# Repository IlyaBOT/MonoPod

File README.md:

# MonoPod

**MonoPod** — самодельный портативный музыкальный плеер в духе классических iPod. Это одновременно учебный проект и личная разработка: электроника, корпус, прошивка и программа для синхронизации музыки с компьютером.

Плеер построен на **ESP32-S3 N16R8**. У него цветной дисплей ST7735S (160 × 128), сенсорное колесо, физические кнопки, microSD, аудиовыход через PCM5102A и синхронизация по USB или Wi-Fi.

## Что лежит в репозитории

| Раздел | Содержимое |
| --- | --- |
| [firmware/](firmware/) | Прошивка для ESP32 / ESP32-S3, инструменты и тесты. Текущая версия: **0.10.7.5**. |
| [desktop/](desktop/) | **MonoPod Desktop 1.3.0** — Windows-приложение для передачи файлов, работы с медиатекой, темами и обновления прошивки. |
| [hardware/](hardware/) | Корпус, 3D-модели, детали для печати и имеющиеся файлы KiCad. |

## Быстрый старт

**Прошивка:** откройте [`firmware/DIY_iPod_Mono/DIY_iPod_Mono.ino`](firmware/DIY_iPod_Mono/DIY_iPod_Mono.ino) в Arduino IDE. Список библиотек, настройки платы и важные ограничения приведены в [инструкции прошивки](firmware/README.md).

**Программа для ПК:** откройте [`desktop/MonoPod.Desktop.sln`](desktop/MonoPod.Desktop.sln) в Visual Studio 2022 или соберите через .NET SDK 8. Подробности — в [desktop/README.md](desktop/README.md).

**Корпус и платы:** начните с [hardware/README.md](hardware/README.md).

## Состояние проекта

Разработка продолжается. Поддержка некоторых возможностей зависит от модели ESP32 и выбранной конфигурации. Например, **Bluetooth Classic/A2DP не поддерживается самим ESP32-S3**; соответствующий режим предназначен для оригинального ESP32.

Прошивка и электроника — прототип: перед повседневным использованием необходима проверка питания, зарядки, подключения аккумулятора и поведения при разряде. Архивы старых версий удалены из текущего дерева, но доступны в истории Git.

## Авторство и лицензии

MonoPod — независимый DIY-проект, вдохновлённый устройствами iPod; он не является продуктом Apple. Лицензионные файлы, включённые в исходники и ресурсы, находятся рядом с ними: [COPYING](firmware/DIY_iPod_Mono/COPYING), [шрифты](firmware/DIY_iPod_Mono/LICENSE-MONOFONT.txt), [компоненты Desktop](desktop/docs/THIRD_PARTY_NOTICES.md). Условия для всех частей репозитория в целом отдельно не заявляются.

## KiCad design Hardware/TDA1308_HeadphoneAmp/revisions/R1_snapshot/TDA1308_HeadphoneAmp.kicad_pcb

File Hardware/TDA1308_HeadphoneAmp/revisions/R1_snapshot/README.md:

# MonoPod: усилитель наушников TDA1308, R1

Создано 27.10.2026 в KiCad 10.0.6. Основной проект: `TDA1308_HeadphoneAmp.kicad_pro`; редактируемые схема и PCB находятся рядом. Папки `libraries/`, таблицы `sym-lib-table` и `fp-lib-table` содержат реальные символы, footprints и модели из установленного KiCad, поэтому проект можно переносить целиком.

## Что выполнено и что подтверждено

- Двухслойная PCB 45 x 25 мм, FR4 1,6 мм. Компоненты сверху; большие электролиты вдоль верхнего края.
- Основа: [NXP TDA1308 Rev.5, Fig.4, стр.6](https://www.nxp.com/docs/en/data-sheet/TDA1308.pdf). Инвертирующие каскады, VREF, питание и полярности сверены по рисунку; различия перечислены в `validation/datasheet_comparison.md`.
- Свежие ERC и DRC: 0 нарушений, 0 незавершённых соединений, 0 расхождений PCB со схемой. Отчёты в `validation/`. Исключения DRC не добавлялись.
- Проверены все площадки и выводы по экспортированному нетлисту, полярности C1/C2/C6/C7, pin 1 U1 и конфигурации ATT/DIRECT. `engineering_audit.json` и `calculations.json` содержат измеренные CAD-параметры и расчёты.
- Это законченные CAD-файлы и производственные экспорты. Физический образец не изготовлен и не испытан. ERC/DRC не подтверждают исправность выпаянной микросхемы, устойчивость с конкретным кабелем, THD, шум или механическое размещение в корпусе MonoPod.

## Питание и провода

Штатно подать стабилизированные 3,3 В. Подача 5 В допустима только после успешных испытаний на стенде; 5 В идут только на эту плату, а не на GPIO ESP32. Не превышать 5 В в этом проекте. Общая земля для питания, PCM5102A и наушников. Разъём 3,5 мм устанавливается отдельно.

| Площадка | Надпись | Назначение |
|---|---|---|
| J1 | VCC | VDD, питание 3,3 В |
| J2 | GND | Земля питания и PCM5102A |
| J3 | LIN | Левый линейный сигнал PCM5102A |
| J4 | RIN | Правый линейный сигнал PCM5102A |
| J5 | GND | Общий контакт наушников |
| J6 | LOUT | Левый контакт наушников, после C6 |
| J7 | ROUT | Правый контакт наушников, после C7 |

Смотреть на лицевую сторону: входные провода слева, выходные справа. Отверстия проводов фактически 1,15 мм, площадки 2,3 мм; AWG26-30 подходят. `D0.9mm` в имени footprint обозначает размер провода, а не диаметр сверла. Закрепить провода от натяжения в корпусе. Монтажных отверстий нет. Провода сигнал/земля вести рядом, вдали от ESP32, антенны и импульсных цепей питания.

## Режим входа: переключать только при снятом питании

| Канал / режим | Установить 0 Ом | Не устанавливать / снять |
|---|---|---|
| L ATTENUATED, по умолчанию | R15, R16 | R19 |
| R ATTENUATED, по умолчанию | R17, R18 | R20 |
| L DIRECT | R19 | R15 И R16 |
| R DIRECT | R20 | R17 И R18 |

R3/R4 и R5/R6 остаются на местах. Две снимаемые перемычки полностью отключают соответствующий делитель и от источника, и от выбранного входа. В DIRECT резистор 3,3 кОм не шунтирует источник. Одновременная установка ATT и DIRECT недопустима; электрической механической защиты от ошибочной пайки нет. Каналы можно конфигурировать отдельно. Вход DIRECT при полной амплитуде PCM5102A вызовет клиппинг: начинать с программно уменьшенной громкости.

Изолированный делитель 10 кОм / 3,3 кОм даёт -12,1 дБ, но вход 3,9 кОм нагружает его. Полная схема в ATT имеет около -16,4 дБ до выходного резистора и -17,0 дБ до наушников 32 Ом на средних частотах. При 2,1 В RMS на входе расчётно получается около 0,298 В RMS / 2,8 мВт на канал. Это расчёт линейной схемы, не измерение громкости и не гарантия максимальной мощности. Оба канала инвертированы одинаково; взаимная полярность стерео сохраняется.

R7/R9 и R8/R10 = 3,9 кОм: номинальное отношение резисторов активной ступени -1. В режиме ATT сопротивление источника дополнительно влияет на суммарное усиление. C4/C5 неполярные, 4,7 мкФ / 25 В X7R 1206; выбрать изделие с фактической ёмкостью не менее 2,2 мкФ при постоянном смещении до 2,5 В. Номинальный входной срез: около 5,3 Гц в ATT и 8,7 Гц в DIRECT при 4,7 мкФ, выше при снижении эффективной ёмкости.

## Конденсаторы и имеющиеся детали

| Ref | Номинал по умолчанию | Место / максимальный диаметр | Полярность |
|---|---|---|---|
| C1 | 22 мкФ, >=10 В | Радиальный D5, шаг 2,0 мм | + к VREF, - к GND |
| C2 | 100 мкФ, >=10 В | Радиальный D6,3, шаг 2,5 мм | + к VDD, - к GND |
| C3 | 100 нФ, 25 В, X7R | 0805 | Неполярный |
| C4/C5 | 4,7 мкФ, 25 В, X7R | 1206 | Неполярные |
| C6/C7 | 220 мкФ, >=10 В | Радиальный D8, шаг 3,5 мм | + к усилителю через R11/R12, - к наушникам |

C6/C7 можно заменить на 470 мкФ / >=10 В в том же габарите. Ваши выпаянные 100 мкФ / 25 В электрически подходят для C2 и как временная замена C6/C7; корпус должен физически помещаться. Для C2 требуется D<=6,3 мм, для C6/C7 D<=8 мм. Шаг 2,5 мм у меньшего конденсатора можно аккуратно развести до 3,5 мм для C6/C7, не нагружая выводы у резиновой пробки. Не изгибать выводы вплотную к корпусу. Монтаж стоя; укладка крупных конденсаторов лёжа внутрь платы не предусмотрена. Высоту и место в корпусе измерить до сборки. 3D-модели библиотечные и не доказывают высоту ваших деталей.

Ёмкость, ESR и утечка выпаянных электролитов неизвестны. Вздутые, высохшие и протекающие детали не использовать. Дефектные выходные конденсаторы тоже могут вызывать искажения и потерю баса.

| C6/C7 | Срез на 32 Ом, без 2,2 Ом | Срез с R11/R12 = 2,2 Ом |
|---|---|---|
| 100 мкФ | 49,7 Гц | 46,5 Гц |
| 220 мкФ | 22,6 Гц | 21,2 Гц |
| 470 мкФ | 10,6 Гц | 9,9 Гц |

На 20 Гц вариант 220 мкФ имеет заметный спад; 470 мкФ лучше сохраняет низкие частоты. Расчёт предполагает резистивную нагрузку 32 Ом. Реальный импеданс наушников зависит от частоты.

Подтверждённый набор пользователя: одна выпаянная SOIC-8 с надписью TDA1308 и электролиты 100 мкФ / 25 В, количество и размеры неизвестны. Для штатной сборки требуются дополнительно C1 22 мкФ x1, C3 100 нФ x1, C4/C5 4,7 мкФ x2 и C6/C7 220 мкФ x2 либо 470 мкФ x2. C2 можно взять из имеющихся 100 мкФ, если он исправен и помещается. Если использовать имеющиеся 100 мкФ на выходах, два новых выходных электролита для первого прототипа не обязательны, но срез будет около 50 Гц.

## Устойчивость и сборка

Схема сохраняет обратную связь NXP до разделительного конденсатора. R9/R10 находятся рядом с U1, их сигнальные цепи проходят сверху. C3 расположен рядом с выводом 8; его GND и вывод 4 входят короткими соединениями в общую землю. На B.Cu залит основной GND, на F.Cu добавлена связанная заливка; отдельные короткие переходы сигналов на нижнюю сторону присутствуют. Разъединённые электрически островки меди удаляются; локальные участки земли соединяются через переходы и верхний слой. Метрики в `engineering_audit.json`.

В даташите указана ёмкостная нагрузка до 200 пФ при его условиях. Не устанавливать большие керамические конденсаторы с RAW-выходов на GND. R11/R12 = 2,2 Ом стоят вне петли обратной связи как места для небольшой выходной развязки; они не гарантируют устойчивость с любым кабелем. Замена на 0 Ом допустима после испытаний. На макете обязательно проверить осциллографом отсутствие ВЧ-возбуждения с реальным кабелем и нагрузкой. Расчётное noise gain в ATT около 1,61, в DIRECT около 2; отдельного гарантированного минимального noise gain даташит не задаёт.

Сначала паять резисторы и C3/C4/C5, затем U1, затем электролиты. По умолчанию ставить 18 резисторов, 7 конденсаторов и U1: всего 26 электронных деталей. R19/R20 не ставить. Девять TP и семь J являются площадками платы, дополнительных деталей не требуют. Полный список с количеством, footprint и режимом установки в `BOM.csv` (UTF-8 BOM, разделитель `;`).

U1: SOIC-8 / SO8, тело примерно 3,9 x 4,9 мм, шаг 1,27 мм. TSSOP-8 с шагом 0,65 мм сюда не подходит. По словам пользователя имеющийся корпус SOIC-8; маркировка TDA1308 сама по себе не доказывает происхождение и исправность. На плате pin 1 U1 находится сверху слева; ориентироваться по метке pin 1 и рисунку assembly. Положительная площадка электролитов квадратная и отмечена `+`; закрашенная половина footprint соответствует отрицательной стороне.

## Первый запуск: без PCM5102A и без наушников

1. При снятом питании проверить пайку, ориентацию U1 и полярности четырёх электролитов. Проверить отсутствие устойчивого короткого VDD-GND мультиметром; из-за зарядки C2 показание сопротивления может меняться. Проверить перемычки режима.
2. Подать стабилизированные 3,3 В от лабораторного источника с начальным ограничением 20 мА. Не подавать аудиосигнал. После зарядки конденсаторов источник должен выйти из ограничения. Нормальный ток покоя ожидается единицы мА (NXP: 3 мА типично, 5 мА максимум при 5 В, плюс ток делителя). Устойчивый ток более 10 мА без сигнала или нагрев требуют выключения и поиска причины.
3. Измерить TP1 VDD и TP3 VREF относительно TP2 GND. VREF должен быть около VDD/2: примерно 1,65 В при 3,3 В. Для начальной диагностики ориентир 1,60-1,70 В при точных 3,3 В; это практический ориентир, не паспортный допуск всей сборки.
4. Измерить постоянное напряжение на выводах 1 и 7 / TP6 и TP7. Оба должны быть около VREF, а не около нуля. Заметная разница между каналами либо выход у шины питания требует проверки U1 и обратной связи. Не подключать наушники к TP6/TP7.
5. Проверить DC после выходных конденсаторов, TP8/TP9. Без нагрузки ждать около 120 с для 220 мкФ, 240 с для 470 мкФ, 60 с для 100 мкФ: постоянная времени с 100 кОм составляет 22/47/10 с. В начале возможен зарядный импульс. После установления ориентир <10 мВ; если напряжение сохраняется, проверить полярность/утечку конденсатора и пайку. Это критерий диагностики, не гарантия для неизвестных электролитов.
6. Подать тестовый синус 1 кГц, например 20 мВ RMS, через LIN/RIN с общей землёй. В ATT ожидается около 3 мВ RMS на наушниковом выходе при резистивной нагрузке, поэтому для оценки формы можно постепенно увеличить до 100-200 мВ RMS на входе. Наблюдать оба RAW-выхода и выходы после C6/C7 осциллографом. Земля щупа только GND. Для проверки ВЧ использовать короткую землю щупа и пробник x10.
7. Установить отдельные эквиваленты нагрузки 330 Ом между LOUT-GND и ROUT-GND; проверить форму, DC и просадку питания. Нагрузки подключать при снятом питании, затем повторять измерения после включения.
8. Заменить эквиваленты на 33 Ом, >=0,25 Вт каждый. Для испытаний с сигналом можно увеличить токовый лимит до 50-100 мА, наблюдая потребление. Начинать с малой амплитуды. Не искать предел громкости в наушниках.
9. Проверить отсутствие клиппинга, ВЧ-самовозбуждения, перегрева и заметного падения VDD; повторить с реальным кабелем и с обоими каналами. Логический анализатор не заменяет осциллограф для DC, аналоговой формы и искажений; учитывать допустимые напряжения его входов.
10. Только после успешных проверок подключить наушники при минимальной громкости и установившемся питании. Затем подключить PCM5102A, начиная с минимального цифрового уровня. При выключениях/включениях учитывать зарядные импульсы. Испытание на 5 В проводить сначала без наушников и повторять весь цикл.

Выпаянная U1 может быть повреждена, перемаркирована или перегрета. Правильная схема и чистый DRC не исключают сохранение прежних симптомов перегруза из-за самой микросхемы. Измеренное улучшение на активных колонках не доказывает её работоспособность на 32 Ом.

## Файлы производства

- `gerbers/`: F.Cu/B.Cu, маски, шелкография, Edge.Cuts; сверловки PTH/NPTH и карты отверстий SVG.
- `manufacturing.zip`: только необходимые Gerber/сверловки, Gerber job и `FABRICATION.txt`. Ничего дополнительно не зеркалить и не масштабировать. Пустой NPTH-файл нормален: нет неплакированных отверстий.
- `renders/front.png`, `renders/back.png`: 3D-виды; `copper_front.svg`, `copper_back.svg`: слои меди; `assembly.svg`: карта компонентов. Изображения не являются файлами изготовления.
- `docs/schematic.pdf`: обзор принципиальной схемы; исходник `.kicad_sch` является редактируемым оригиналом.
- `validation/`: свежие проверки, полный нетлист, контроль карт выводов, расчёты и SHA-256 файлов.

Параметры заказа: 45 x 25 мм, 2 слоя, FR4 1,6 мм, медь 35 мкм, обычная маска и шелкография с двух сторон, стандартный паяемый финиш. Минимальные дорожки 0,25 мм, зазоры 0,20 мм; via 0,65/0,30 мм. Допуски и минимумы выбранного производителя нужно сопоставить с этими параметрами. Заказ и изготовление не выполнялись.

Для повторной проверки на этом ПК: `kicad-cli sch erc --severity-all --exit-code-violations TDA1308_HeadphoneAmp.kicad_sch` и `kicad-cli pcb drc --schematic-parity --all-track-errors --severity-all --exit-code-violations TDA1308_HeadphoneAmp.kicad_pcb`. Если CLI отсутствует в PATH, использовать `C:\Program Files\KiCad\10.0\bin\kicad-cli.exe`. Генераторы в `scripts/` сохраняют инженерное происхождение проекта и при запуске перезаписывают файлы; для обычного редактирования открывать нативные файлы KiCad.

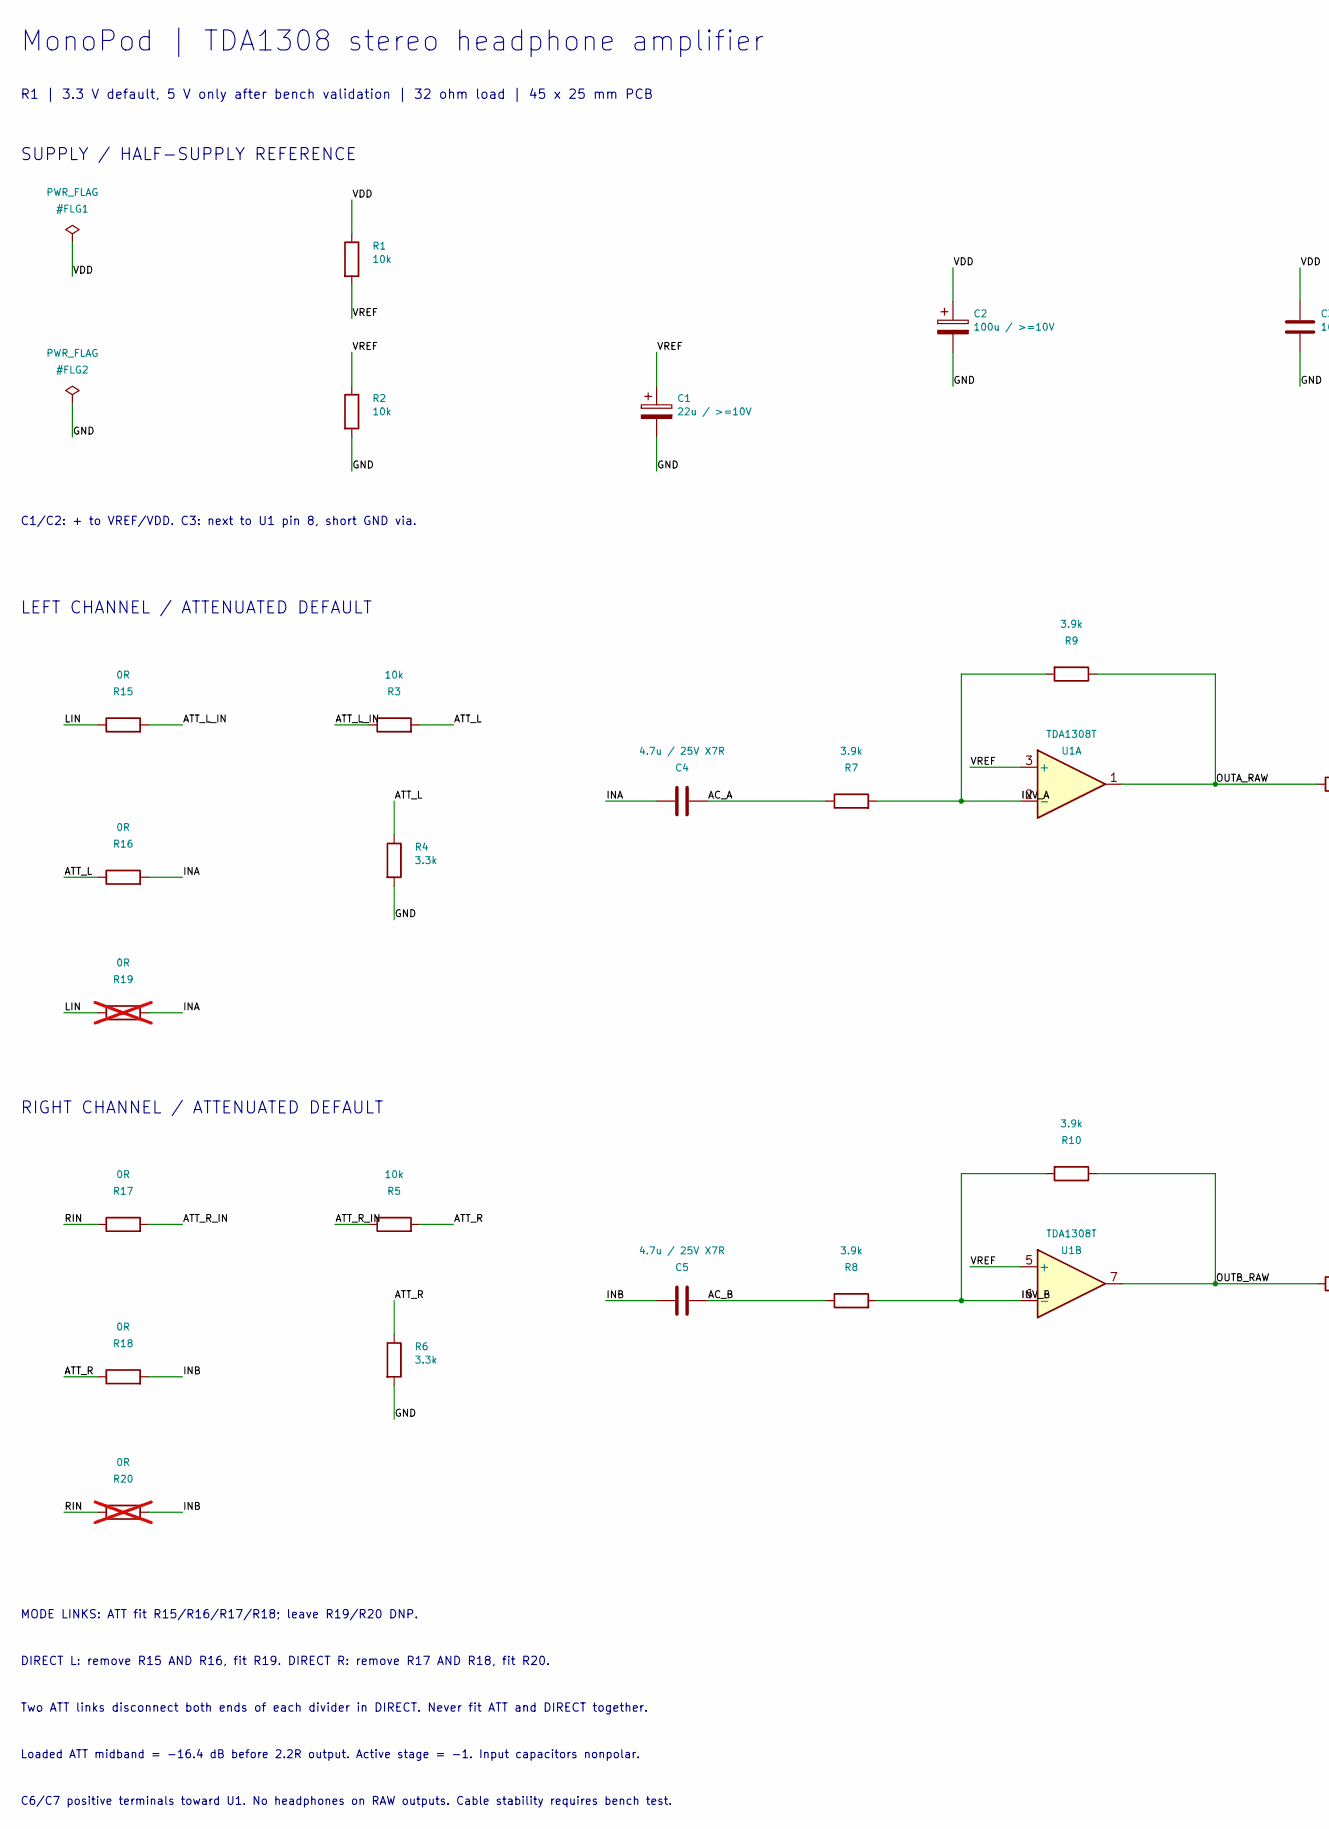
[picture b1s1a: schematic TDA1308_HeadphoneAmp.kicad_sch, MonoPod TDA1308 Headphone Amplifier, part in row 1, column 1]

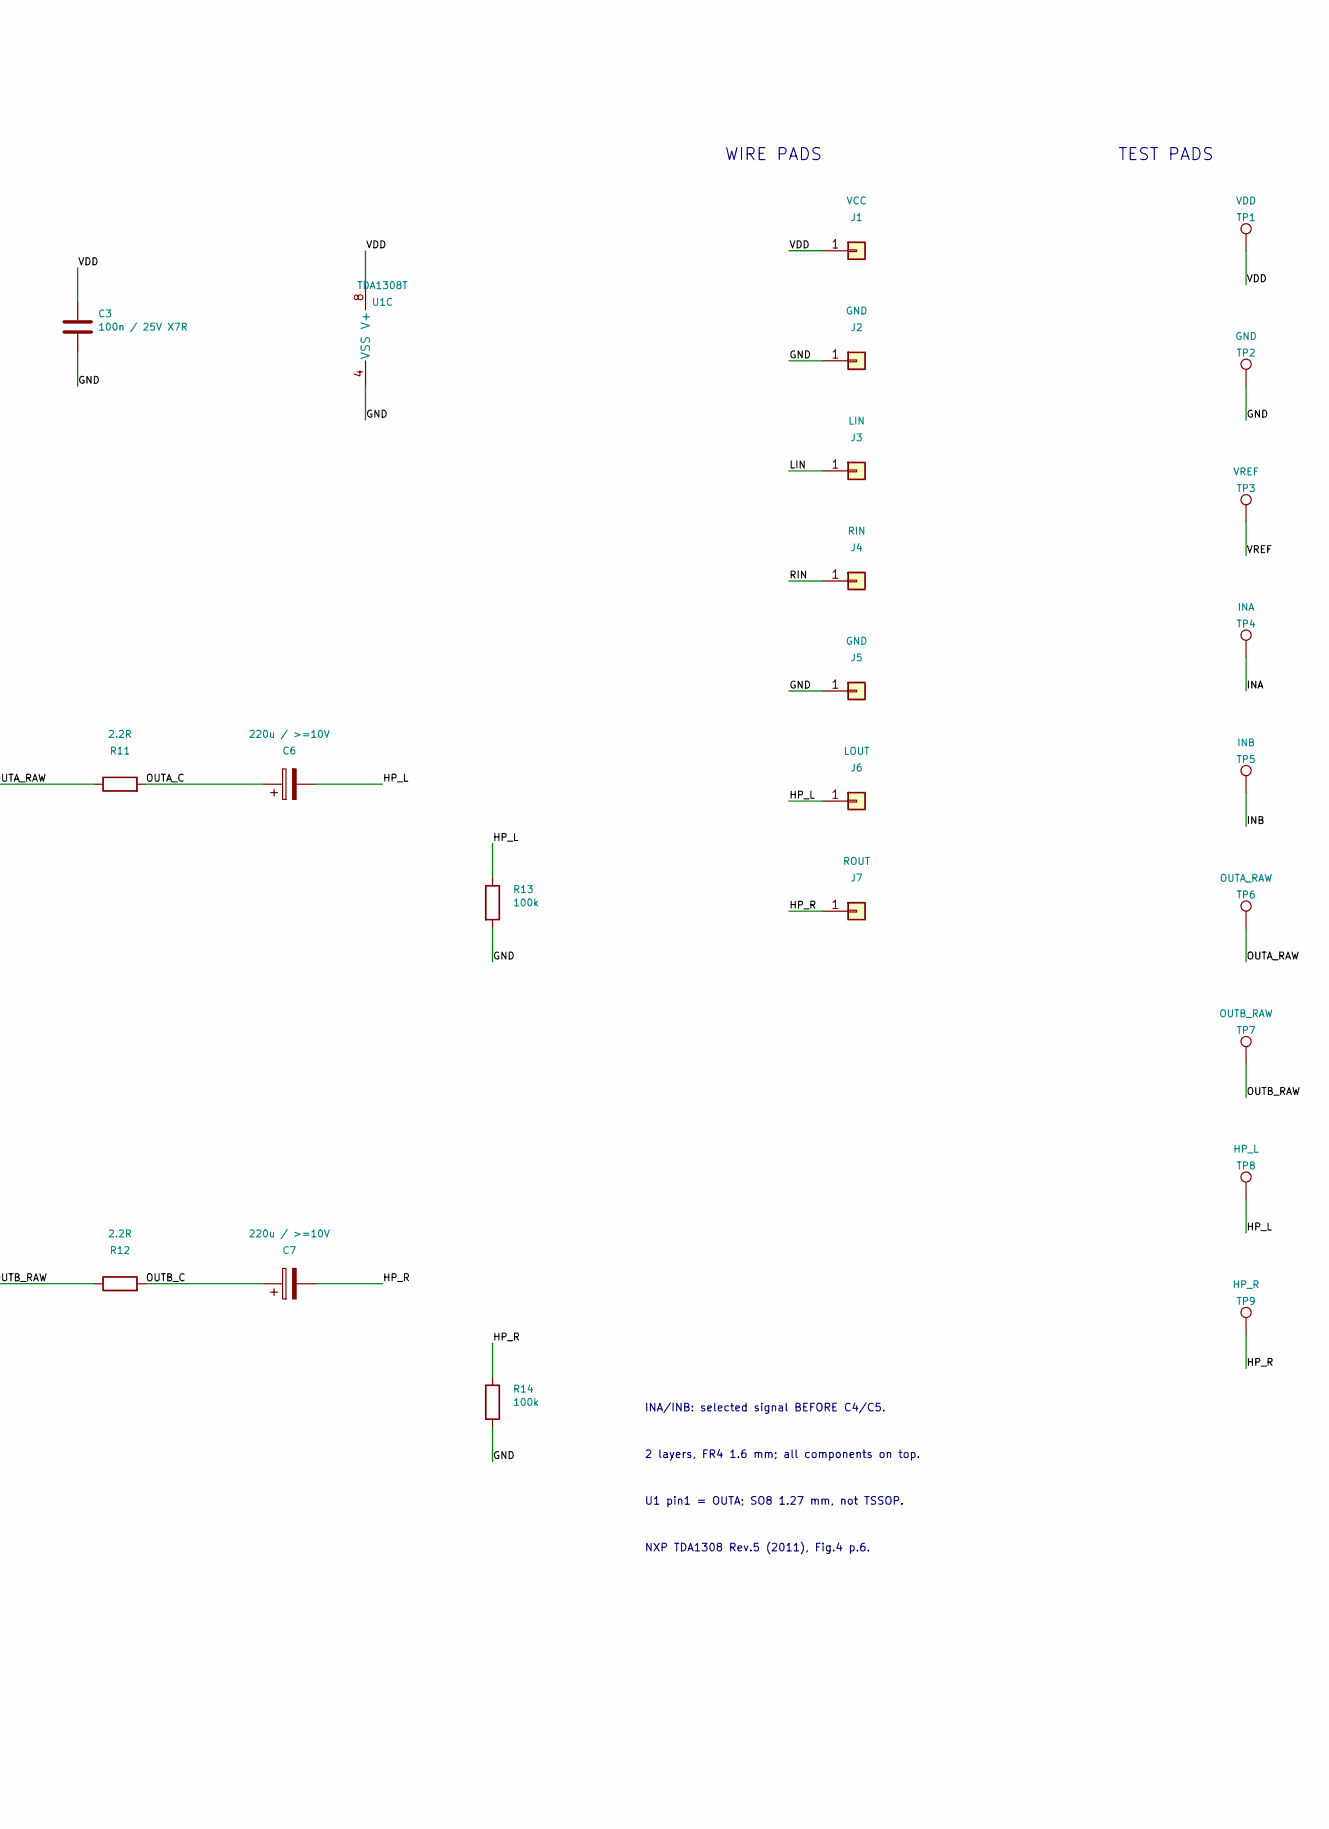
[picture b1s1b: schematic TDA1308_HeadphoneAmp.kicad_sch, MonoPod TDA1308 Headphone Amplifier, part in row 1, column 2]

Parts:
C1: 22u / >=10V; CP_Radial_D5.0mm_P2.00mm
C2: 100u / >=10V; CP_Radial_D6.3mm_P2.50mm
C3: 100n / 25V X7R; C_0805_2012Metric
C4, C5: 4.7u / 25V X7R; C_1206_3216Metric
C6, C7: 220u / >=10V; CP_Radial_D8.0mm_P3.50mm
J1: VCC; SolderWire-0.5sqmm_1x01_D0.9mm_OD2.1mm
J2, J5: GND; SolderWire-0.5sqmm_1x01_D0.9mm_OD2.1mm
J3: LIN; SolderWire-0.5sqmm_1x01_D0.9mm_OD2.1mm
J4: RIN; SolderWire-0.5sqmm_1x01_D0.9mm_OD2.1mm
J6: LOUT; SolderWire-0.5sqmm_1x01_D0.9mm_OD2.1mm
J7: ROUT; SolderWire-0.5sqmm_1x01_D0.9mm_OD2.1mm
R1, R2, R3, R5: 10k; R_0805_2012Metric
R4, R6: 3.3k; R_0805_2012Metric
R7, R8, R9, R10: 3.9k; R_0805_2012Metric
R11, R12: 2.2R; R_0805_2012Metric
R13, R14: 100k; R_0805_2012Metric
R15, R16, R17, R18: 0R; R_0805_2012Metric
R19, R20: 0R; R_0805_2012Metric; not fitted
TP1: VDD; TestPoint_Pad_D1.5mm
TP2: GND; TestPoint_Pad_D1.5mm
TP3: VREF; TestPoint_Pad_D1.5mm
TP4: INA; TestPoint_Pad_D1.5mm
TP5: INB; TestPoint_Pad_D1.5mm
TP6: OUTA_RAW; TestPoint_Pad_D1.5mm
TP7: OUTB_RAW; TestPoint_Pad_D1.5mm
TP8: HP_L; TestPoint_Pad_D1.5mm
TP9: HP_R; TestPoint_Pad_D1.5mm
U1: TDA1308T; SOIC-8_3.9x4.9mm_P1.27mm

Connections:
/AC_A: C4.2, R7.1
/AC_B: C5.2, R8.1
/ATT_L: R3.2, R4.1, R16.1
/ATT_L_IN: R3.1, R15.2
/ATT_R: R5.2, R6.1, R18.1
/ATT_R_IN: R5.1, R17.2
/GND: C1.2, C2.2, C3.2, J2.1, J5.1, R2.2, R4.2, R6.2, R13.2, R14.2, TP2.1, U1.4 (VSS)
/HP_L: C6.2, J6.1, R13.1, TP8.1
/HP_R: C7.2, J7.1, R14.1, TP9.1
/INA: C4.1, R16.2, R19.2, TP4.1
/INB: C5.1, R18.2, R20.2, TP5.1
/INV_A: R7.2, R9.2, U1.2 (-)
/INV_B: R8.2, R10.2, U1.6 (-)
/LIN: J3.1, R15.1, R19.1
/OUTA_C: C6.1, R11.2
/OUTA_RAW: R9.1, R11.1, TP6.1, U1.1
/OUTB_C: C7.1, R12.2
/OUTB_RAW: R10.1, R12.1, TP7.1, U1.7
/RIN: J4.1, R17.1, R20.1
/VDD: C2.1, C3.1, J1.1, R1.1, TP1.1, U1.8 (V+)
/VREF: C1.1, R1.2, R2.1, TP3.1, U1.3 (+), U1.5 (+)

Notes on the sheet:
MonoPod | TDA1308 stereo headphone amplifier
R1 | 3.3 V default, 5 V only after bench validation | 32 ohm load | 45 x 25 mm PCB
SUPPLY / HALF-SUPPLY REFERENCE
C1/C2: + to VREF/VDD. C3: next to U1 pin 8, short GND via.
LEFT CHANNEL / ATTENUATED DEFAULT
RIGHT CHANNEL / ATTENUATED DEFAULT
MODE LINKS: ATT fit R15/R16/R17/R18; leave R19/R20 DNP.
DIRECT L: remove R15 AND R16, fit R19. DIRECT R: remove R17 AND R18, fit R20.
Two ATT links disconnect both ends of each divider in DIRECT. Never fit ATT and DIRECT together.
Loaded ATT midband = -16.4 dB before 2.2R output. Active stage = -1. Input capacitors nonpolar.
C6/C7 positive terminals toward U1. No headphones on RAW outputs. Cable stability requires bench test.
WIRE PADS
TEST PADS
INA/INB: selected signal BEFORE C4/C5.
2 layers, FR4 1.6 mm; all components on top.
U1 pin1 = OUTA; SO8 1.27 mm, not TSSOP.
NXP TDA1308 Rev.5 (2011), Fig.4 p.6.

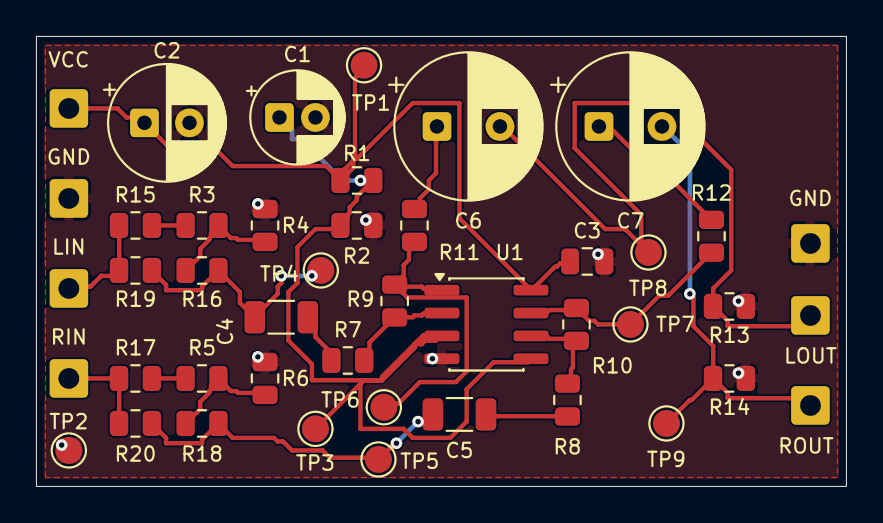
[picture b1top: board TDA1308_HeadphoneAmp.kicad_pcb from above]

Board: 2 copper layers, 45.0 x 25.0 mm, 44 parts (0 on the bottom side), 21 nets.

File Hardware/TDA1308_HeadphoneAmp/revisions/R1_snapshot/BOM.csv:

References;Value;Footprint;Quantity;Fit_default;Notes
U1;TDA1308T;Package_SO:SOIC-8_3.9x4.9mm_P1.27mm;1;YES;"U1: SO8, salvaged chip marked TDA1308; functionality unverified"
R1,R2,R3,R5;10k;Resistor_SMD:R_0805_2012Metric;4;YES;R1: VREF upper divider, 1% | R2: VREF lower divider, 1% | R3: Left attenuation series, 1% | R5: Right attenuation series, 1%
R4,R6;3.3k;Resistor_SMD:R_0805_2012Metric;2;YES;R4: Left attenuation shunt, 1% | R6: Right attenuation shunt, 1%
R7,R8,R9,R10;3.9k;Resistor_SMD:R_0805_2012Metric;4;YES;R7: Left input, 1% | R8: Right input, 1% | R9: Left feedback, 1% | R10: Right feedback, 1%
R11,R12;2.2R;Resistor_SMD:R_0805_2012Metric;2;YES;R11: Left output isolation, 0R permitted after bench test | R12: Right output isolation, 0R permitted after bench test
R13,R14;100k;Resistor_SMD:R_0805_2012Metric;2;YES;R13: Left output bleed | R14: Right output bleed
R15,R16,R17,R18;0R;Resistor_SMD:R_0805_2012Metric;4;YES;R15: ATT L input link, FIT default | R16: ATT L output link, FIT default | R17: ATT R input link, FIT default | R18: ATT R output link, FIT default
R19,R20;0R;Resistor_SMD:R_0805_2012Metric;2;DNP;"R19: DIRECT L, DNP default; remove R15/R16 before fitting | R20: DIRECT R, DNP default; remove R17/R18 before fitting"
C1;22u / >=10V;Capacitor_THT:CP_Radial_D5.0mm_P2.00mm;1;YES;C1: VREF, plus pin1
C2;100u / >=10V;Capacitor_THT:CP_Radial_D6.3mm_P2.50mm;1;YES;"C2: Supply bulk, plus pin1; 100u 25V possible if size fits"
C3;100n / 25V X7R;Capacitor_SMD:C_0805_2012Metric;1;YES;"C3: Local bypass next to U1 pin8; nearby GND via to pin4 return plane"
C4,C5;4.7u / 25V X7R;Capacitor_SMD:C_1206_3216Metric;2;YES;"C4: Nonpolar input; effective capacitance >=2.2u at bias | C5: Nonpolar input; effective capacitance >=2.2u at bias"
C6,C7;220u / >=10V;Capacitor_THT:CP_Radial_D8.0mm_P3.50mm;2;YES;"C6: Left output, plus pin1 toward IC; 470u or 100u25V alternatives | C7: Right output, plus pin1 toward IC; 470u or 100u25V alternatives"
J1-J7;Wire landing only;Connector_Wire:SolderWire-0.5sqmm_1x01_D0.9mm_OD2.1mm;7;PCB ONLY;"No connector purchase; actual plated drill 1.15 mm; AWG26-30"
TP1-TP9;Exposed test pad;TestPoint:TestPoint_Pad_D1.5mm;9;PCB ONLY;No component purchase

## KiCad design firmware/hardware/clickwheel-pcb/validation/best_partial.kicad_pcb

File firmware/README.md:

# MonoPod Firmware

**Версия: 0.10.7.5** · ESP32 / ESP32-S3 · Arduino C++

Прошивка отвечает за экран, колесо, кнопки, проигрывание музыки с microSD, настройки и синхронизацию с MonoPod Desktop.

## Как собрать

1. Установите **Arduino IDE 2.x** и поддержку плат **Arduino-ESP32 3.x**.
2. Установите библиотеки **Adafruit GFX**, **Adafruit ST7735 and ST7789 Library**, **ESP8266Audio**. В коде также предусмотрены условные зависимости для некоторых аппаратных возможностей.
3. Откройте [`DIY_iPod_Mono/DIY_iPod_Mono.ino`](DIY_iPod_Mono/DIY_iPod_Mono.ino).
4. В Arduino IDE выберите **ESP32-S3** (для прототипа N16R8: Flash 16 MB, PSRAM 8 MB / OPI) или классическую ESP32, если собираете под старую плату.
5. Проверьте параметры платы и подключение модулей по [`Config.h`](DIY_iPod_Mono/Config.h) **до прошивки**. Пины двух аппаратных профилей различаются.
6. Скомпилируйте скетч. Для обновления по OTA требуется подходящая таблица разделов; пример — [`tools/partitions/`](tools/partitions/).

Распиновка и значения резисторов определены в `Config.h`; не ориентируйтесь на картинки ранних прототипов.

## Функции

- Списки музыки и метаданные MP3/FLAC; кэш медиатеки MonoPodDB.
- Аудиовыход I²S через PCM5102A; сенсорное колесо и резистивная клавиатура.
- Синхронизация файлов по Wi-Fi и USB CDC; встроенные настройки и диагностика.
- Часы, темы оформления и экспериментальное OTA-обновление.
- Bluetooth Classic/A2DP — **только для оригинального ESP32**. На ESP32-S3 его нет.

## Структура

- `DIY_iPod_Mono/` — рабочий Arduino-проект: `.ino`, `.cpp` и `.h`.
- `tests/` — тесты для ПК; они не заменяют проверку на физическом устройстве.
- `tools/` — конвертеры, утилиты и файлы конфигурации.
- `docs/` — [краткая история изменений](docs/CHANGELOG.md) и технические пояснения.

## Важно для прототипа

При просадке шины 3,3 В встроенная защита прошивки **не заменяет** исправный стабилизатор, аппаратную защиту аккумулятора и корректное питание. Режим HOLD/Deep Sleep и его ограничения описаны [здесь](docs/POWER_GUARD_HOLD_RU.md).

USB CDC и USB Mass Storage — разные режимы. В текущем проекте MSC экспериментален и не является обычным режимом синхронизации с Desktop.

Документация описывает исходники, но **не утверждает, что версия 0.10.7.5 проверена на реальном ESP32-S3**. Перед обновлением устройства сделайте резервную копию microSD.

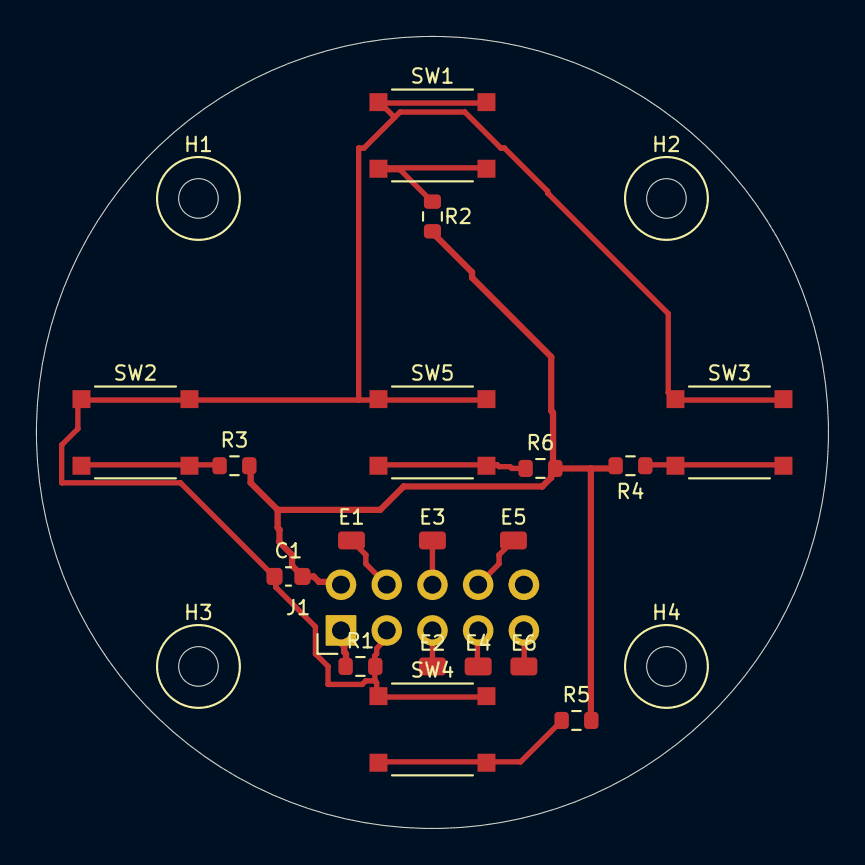
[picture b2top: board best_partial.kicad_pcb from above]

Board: 2 copper layers, 44.0 x 44.0 mm, 23 parts (0 on the bottom side), 14 nets.

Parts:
C1: 100n; C_0603
E1: TOUCH1; TouchWire_2x1p5
E2: TOUCH2; TouchWire_2x1p5
E3: TOUCH3; TouchWire_2x1p5
E4: TOUCH4; TouchWire_2x1p5
E5: TOUCH5; TouchWire_2x1p5
E6: TOUCH6; TouchWire_2x1p5
H1, H2, H3, H4: M2 / 2.2 NPTH; Mount_M2_Keepout5
J1: WIRE / 2x05 P2.54; Header_2x05_P2p54_TopOnly
R1, R5: 10k; R_0603
R2: 0R; R_0603
R3: 2.2k; R_0603
R4: 4.7k; R_0603
R6: 22k; R_0603
SW1: MENU; TS1187A_4x4x0p8_REF
SW2: PREV; TS1187A_4x4x0p8_REF
SW3: NEXT; TS1187A_4x4x0p8_REF
SW4: PLAY; TS1187A_4x4x0p8_REF
SW5: SELECT; TS1187A_4x4x0p8_REF

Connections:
/3V3: J1.1, R1.1
/BTN_ADC: C1.1, J1.3, R1.2, SW1.1, SW2.1, SW3.1, SW4.1, SW5.1
/GND: C1.2, J1.2, R2.2, R3.2, R4.2, R5.2, R6.2
/MENU_RET: R2.1, SW1.2
/NEXT_RET: R4.1, SW3.2
/PLAY_RET: R5.1, SW4.2
/PREV_RET: R3.1, SW2.2
/SELECT_RET: R6.1, SW5.2
/TOUCH1: E1.1, J1.4
/TOUCH2: E2.1, J1.5
/TOUCH3: E3.1, J1.6
/TOUCH4: E4.1, J1.7
/TOUCH5: E5.1, J1.8
/TOUCH6: E6.1, J1.9

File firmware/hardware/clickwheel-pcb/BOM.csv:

References,Quantity,Value,MPN,Footprint / description,Notes
SW1-SW5,5,TS-1187A low-profile 4x4x0.8,User kit / manufacturer unconfirmed,ClickWheel:TS1187A_4x4x0p8_REF,Verify land pattern and contact pairing before fabrication
R1,1,10k,RC0603FR-0710KL,ClickWheel:R_0603,"1%, 0603 (0R jumper tolerance not applicable)"
R2,1,0R,RC0603JR-070RL,ClickWheel:R_0603,Required MENU 0 ohm link
R3,1,2.2k,RC0603FR-072K2L,ClickWheel:R_0603,"1%, 0603 (0R jumper tolerance not applicable)"
R4,1,4.7k,RC0603FR-074K7L,ClickWheel:R_0603,"1%, 0603 (0R jumper tolerance not applicable)"
R5,1,10k,RC0603FR-0710KL,ClickWheel:R_0603,"1%, 0603 (0R jumper tolerance not applicable)"
R6,1,22k,RC0603FR-0722KL,ClickWheel:R_0603,"1%, 0603 (0R jumper tolerance not applicable)"
C1,1,100n,GRM188R71H104KA93D,ClickWheel:C_0603,X7R 50V +/-10%
J1,0,PCB feature / DNP,,10 bare PTH holes; optional underside 2x05 P2.54 header NOT populated,No connector supplied
E1-E6,0,PCB feature / DNP,,"PCB wire lands only, not purchased parts",No connector supplied
H1-H4,0,PCB feature / DNP,,PCB NPTH mounting holes only,No connector supplied
